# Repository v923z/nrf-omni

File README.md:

# nrf-omni
Hand-solderable carrier boards for the NRF52840 chip, exposing all pins

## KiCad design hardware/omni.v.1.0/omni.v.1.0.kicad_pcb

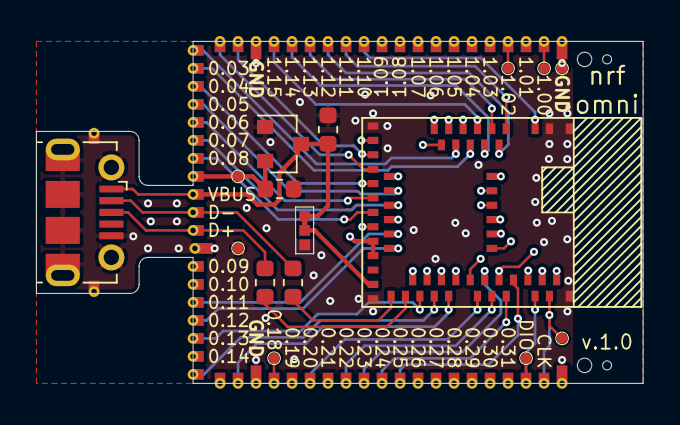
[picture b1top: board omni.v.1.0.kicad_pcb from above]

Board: 4 copper layers, 33.7 x 19.0 mm, 81 parts (0 on the bottom side), 58 nets.

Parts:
C101, C102: 10uF; C_0603_1608Metric
H101, H102: 0.5mm; AlignmentHole_0.5mm
H103, H104: 0.8mm; AlignmentHole_0.8mm
J101: USB_B_Micro; USB_Micro-B_Molex-105017-0001
JP101: SolderJumper_3_Bridged12; SolderJumper-3-Bridged12_0.6x0.6mm
R101, R102: 22R; R_0603_1608Metric
TP101: 1.10; cast-0.6
TP102: 1.11; cast-0.6
TP103: 1.12; cast-0.6
TP104: 1.13; cast-0.6
TP105: 1.14; cast-0.6
TP106: 1.15; cast-0.6
TP107: 0.03; cast-0.6
TP108: 0.29; cast-0.6
TP109: 0.02; cast-0.6
TP110: 0.31; cast-0.6
TP111: 0.28; cast-0.6
TP112: 0.30; cast-0.6
TP113: 0.27; cast-0.6
TP114: 0.00; cast-0.6
TP115: 0.01; cast-0.6
TP116: 0.26; cast-0.6
TP117: 0.04; cast-0.6
TP118: 0.05; cast-0.6
TP119: 0.06; cast-0.6
TP120: 0.07; cast-0.6
TP121: 0.08; cast-0.6
TP122: 1.08; cast-0.6
TP123: 1.09; cast-0.6
TP124: 0.11; cast-0.6
TP125: 1.01; cast-0.6
TP126: 1.03; cast-0.6
TP127: 1.05; cast-0.6
TP128: 1.07; cast-0.6
TP129: 1.06; cast-0.6
TP130: 1.04; cast-0.6
TP131: 0.10; cast-0.6
TP132: CLK; cast-0.6
TP133: 0.09; cast-0.6
TP134: DIO; cast-0.6
TP135: 1.02; cast-0.6
TP136: 0.25; cast-0.6
TP137: 0.24; cast-0.6
TP138: 1.00; cast-0.6
TP139: 0.22; cast-0.6
TP140: 0.23; cast-0.6
TP141: 0.20; cast-0.6
TP142: 0.21; cast-0.6
TP143: 0.19; cast-0.6
TP144: 0.17; cast-0.6
TP145: 0.15; cast-0.6
TP146: 0.16; cast-0.6
TP147: 0.13; cast-0.6
TP148: 0.14; cast-0.6
TP149, TP150, TP151, TP152, TP157: GND; cast-0.6-1.0
TP153: D+; cast-0.6
TP154: D-; cast-0.6
TP155: VBUS; cast-0.6
TP156: 0.12; cast-0.6
TP158: 3V3; cast-0.6
TP159: 0.18; cast-0.6
TP160, TP161: GND; cast-0.6
TP162: SWCH; TestPoint_Pad_D0.6mm
TP163: CLK; TestPoint_Pad_D0.6mm
TP164: DIO; TestPoint_Pad_D0.6mm
TP165: SWO; TestPoint_Pad_D0.6mm
TP166: RST; TestPoint_Pad_D0.6mm
TP167: 3V3; TestPoint_Pad_D0.6mm
TP168, TP169: GND; TestPoint_Pad_D0.6mm
U101: MDBT50Q-1MV2; MDBT50Q1MV2
U102: MCP1703A-4002_SOT23; SOT-23

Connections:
+3V3: C102.1, TP158.1, TP167.1, U101.28, U101.30, U102.2
GND: C101.1, C102.2, J101.5, J101.6, JP101.3, TP149.1, TP150.1, TP151.1, TP152.1, TP157.1, TP160.1, TP161.1, TP168.1, TP169.1, U101.1, U101.2, U101.15, U101.33, U101.55, U102.1
unnamed: C101.2, J101.1, JP101.1, TP155.1, U102.3
unnamed: J101.2, R102.1, TP154.1
unnamed: J101.3, R101.2, TP153.1
unnamed: JP101.2, U101.32
unnamed: R101.1, U101.35
unnamed: R102.2, U101.34
unnamed: TP101.1, U101.3
unnamed: TP102.1, U101.4
unnamed: TP103.1, U101.5
unnamed: TP104.1, U101.6
unnamed: TP105.1, U101.7
unnamed: TP106.1, U101.8
unnamed: TP107.1, U101.9
unnamed: TP108.1, U101.10
unnamed: TP109.1, U101.11
unnamed: TP110.1, U101.12
unnamed: TP111.1, U101.13
unnamed: TP112.1, U101.14
unnamed: TP113.1, U101.16
unnamed: TP114.1, U101.17
unnamed: TP115.1, U101.18
unnamed: TP116.1, U101.19
unnamed: TP117.1, U101.20
unnamed: TP118.1, U101.21
unnamed: TP119.1, U101.22
unnamed: TP120.1, U101.23
unnamed: TP121.1, U101.24
unnamed: TP122.1, U101.25
unnamed: TP123.1, U101.26
unnamed: TP124.1, U101.27
unnamed: TP125.1, U101.61
unnamed: TP126.1, U101.60
unnamed: TP127.1, U101.59
unnamed: TP128.1, U101.58
unnamed: TP129.1, U101.57
unnamed: TP130.1, U101.56
unnamed: TP131.1, U101.54
unnamed: TP132.1, TP163.1, U101.53
unnamed: TP133.1, U101.52
unnamed: TP134.1, TP164.1, U101.51
unnamed: TP135.1, TP162.1, U101.50
unnamed: TP136.1, U101.49
unnamed: TP137.1, U101.48
unnamed: TP138.1, TP165.1, U101.47
unnamed: TP139.1, U101.46
unnamed: TP140.1, U101.45
unnamed: TP141.1, U101.44
unnamed: TP142.1, U101.43
unnamed: TP143.1, U101.42
unnamed: TP144.1, U101.41
unnamed: TP145.1, U101.39
unnamed: TP146.1, U101.38
unnamed: TP147.1, U101.37
unnamed: TP148.1, U101.36
unnamed: TP156.1, U101.29
unnamed: TP159.1, TP166.1, U101.40

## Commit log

2020-06-07 added licence file
2020-06-08 added land pattern for carrier board
2020-06-08 added licence information to footprints
2020-06-09 moved castellated holes closer to edge cut

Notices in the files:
hardware/omni.v.1.0/omni.v.1.0.kicad_pcb:
The MIT licence
